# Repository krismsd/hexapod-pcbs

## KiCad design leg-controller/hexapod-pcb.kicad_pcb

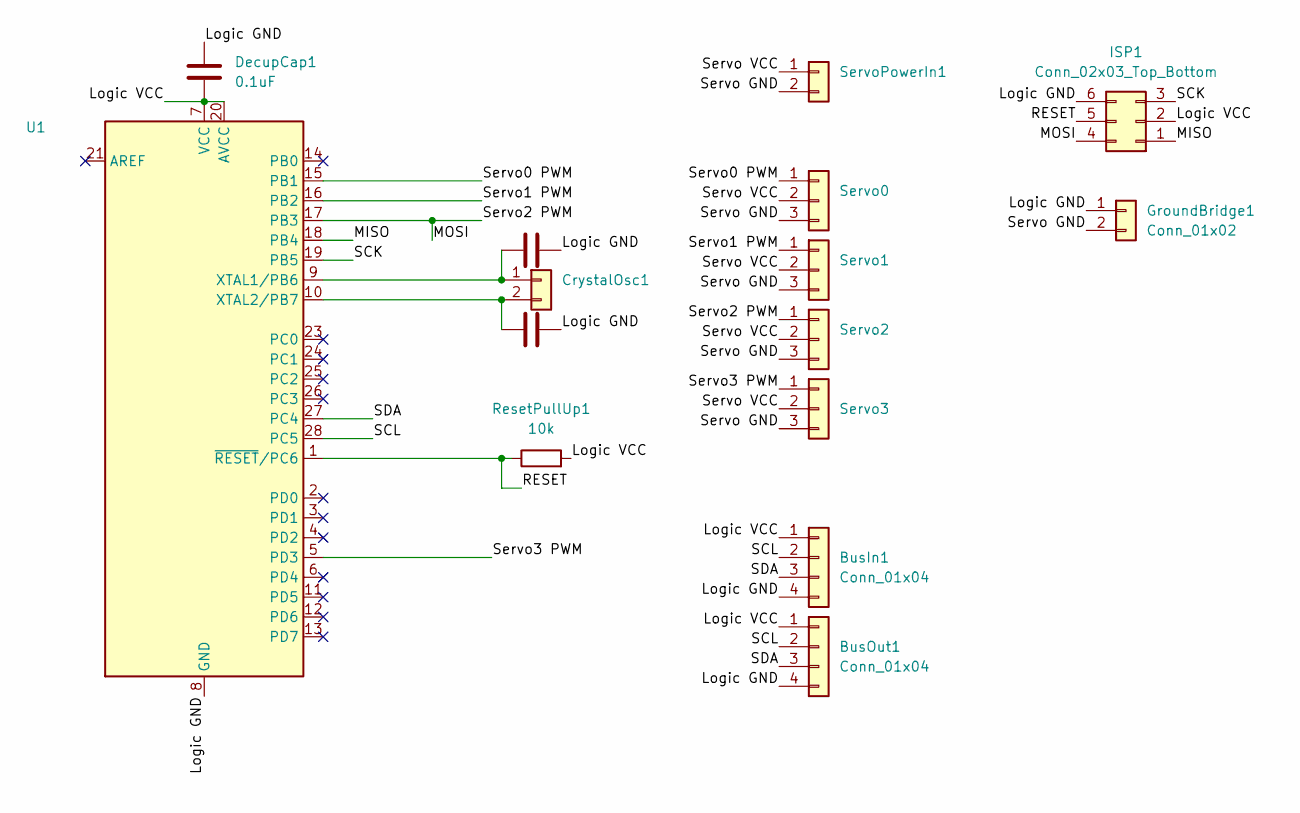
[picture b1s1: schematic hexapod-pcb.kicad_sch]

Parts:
BusIn1: Conn_01x04; Molex_KK-254_AE-6410-04A_1x04_P2.54mm_Vertical
BusOut1: Conn_01x04; Molex_KK-254_AE-6410-04A_1x04_P2.54mm_Vertical
CrystalOsc1: Conn_01x02; Crystal_HC49-4H_Vertical
DecupCap1: 0.1uF; C_Disc_D4.3mm_W1.9mm_P5.00mm
GroundBridge1: Conn_01x02; PinHeader_1x02_P2.54mm_Vertical
ISP1: Conn_02x03_Top_Bottom; PinHeader_2x03_P2.54mm_Vertical
OscCap1, OscCap2: (no value)
ResetPullUp1: 10k; R_Axial_DIN0204_L3.6mm_D1.6mm_P5.08mm_Horizontal
Servo0, Servo1, Servo2, Servo3: Conn_01x03; PinHeader_1x03_P2.54mm_Horizontal
ServoPowerIn1: Conn_01x02; Molex_KK-254_AE-6410-02A_1x02_P2.54mm_Vertical
U1: ATmega328-P; DIP-28_W7.62mm_Socket

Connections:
/Logic GND: BusIn1.4, BusOut1.4, DecupCap1.1, GroundBridge1.1, ISP1.6, OscCap1.2, OscCap2.2, U1.8 (GND), U1.22 (GND); also elsewhere on the board
/Logic VCC: BusIn1.1, BusOut1.1, DecupCap1.2, ISP1.2, ResetPullUp1.2, U1.7 (VCC), U1.20 (AVCC); also elsewhere on the board
/MISO: ISP1.1, U1.18 (PB4); also elsewhere on the board
/MOSI: ISP1.4, Servo2.1, U1.17 (PB3); also elsewhere on the board
/RESET: ISP1.5, ResetPullUp1.1, U1.1 (~RESET/PC6); also elsewhere on the board
/SCK: ISP1.3, U1.19 (PB5); also elsewhere on the board
/SCL: BusIn1.2, BusOut1.2, U1.28 (PC5)
/SDA: BusIn1.3, BusOut1.3, U1.27 (PC4)
/Servo0 PWM: Servo0.1, U1.15 (PB1)
/Servo1 PWM: Servo1.1, U1.16 (PB2)
/Servo3 PWM: Servo3.1, U1.5 (PD3)
/Servo GND: GroundBridge1.2, Servo0.3, Servo1.3, Servo2.3, Servo3.3, ServoPowerIn1.2
/Servo VCC: Servo0.2, Servo1.2, Servo2.2, Servo3.2, ServoPowerIn1.1
unnamed: CrystalOsc1.1, OscCap1.1, U1.9 (XTAL1/PB6)
unnamed: CrystalOsc1.2, OscCap2.1, U1.10 (XTAL2/PB7)

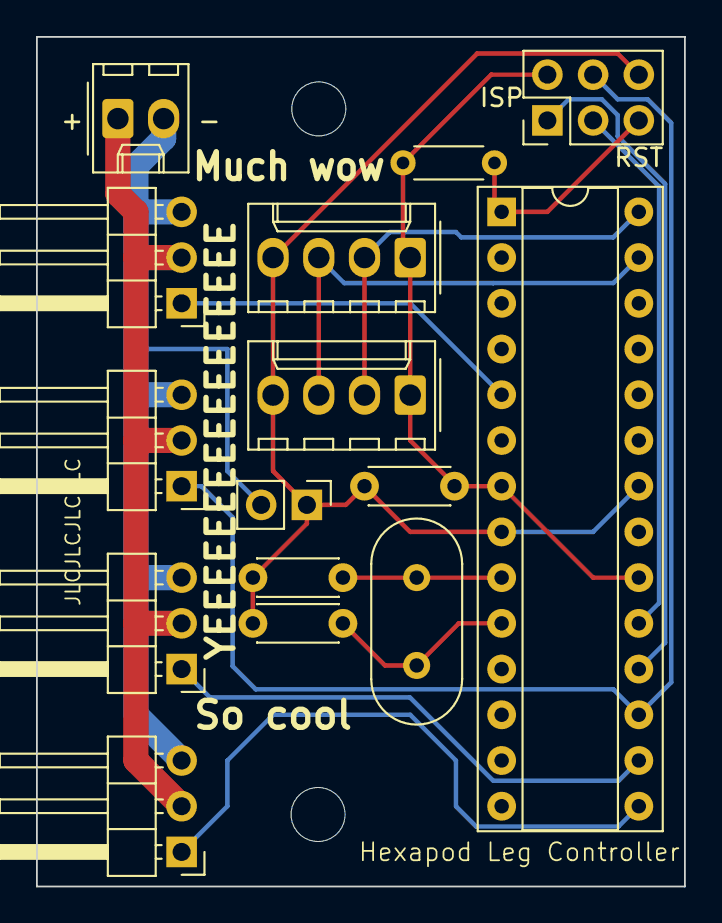
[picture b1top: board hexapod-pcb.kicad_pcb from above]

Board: 2 copper layers, 36.0 x 47.2 mm, 15 parts (0 on the bottom side), 15 nets.

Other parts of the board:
ISP: Conn_02x03_Top_Bottom; PinHeader_2x03_P2.54mm_Vertical

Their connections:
/Logic GND: ISP.6; also elsewhere on the board
/Logic VCC: ISP.2; also elsewhere on the board
/MISO: ISP.1; also elsewhere on the board
/MOSI: ISP.4; also elsewhere on the board
/RESET: ISP.5; also elsewhere on the board
/SCK: ISP.3; also elsewhere on the board

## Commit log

2023-08-03 Leg Controller PCB
